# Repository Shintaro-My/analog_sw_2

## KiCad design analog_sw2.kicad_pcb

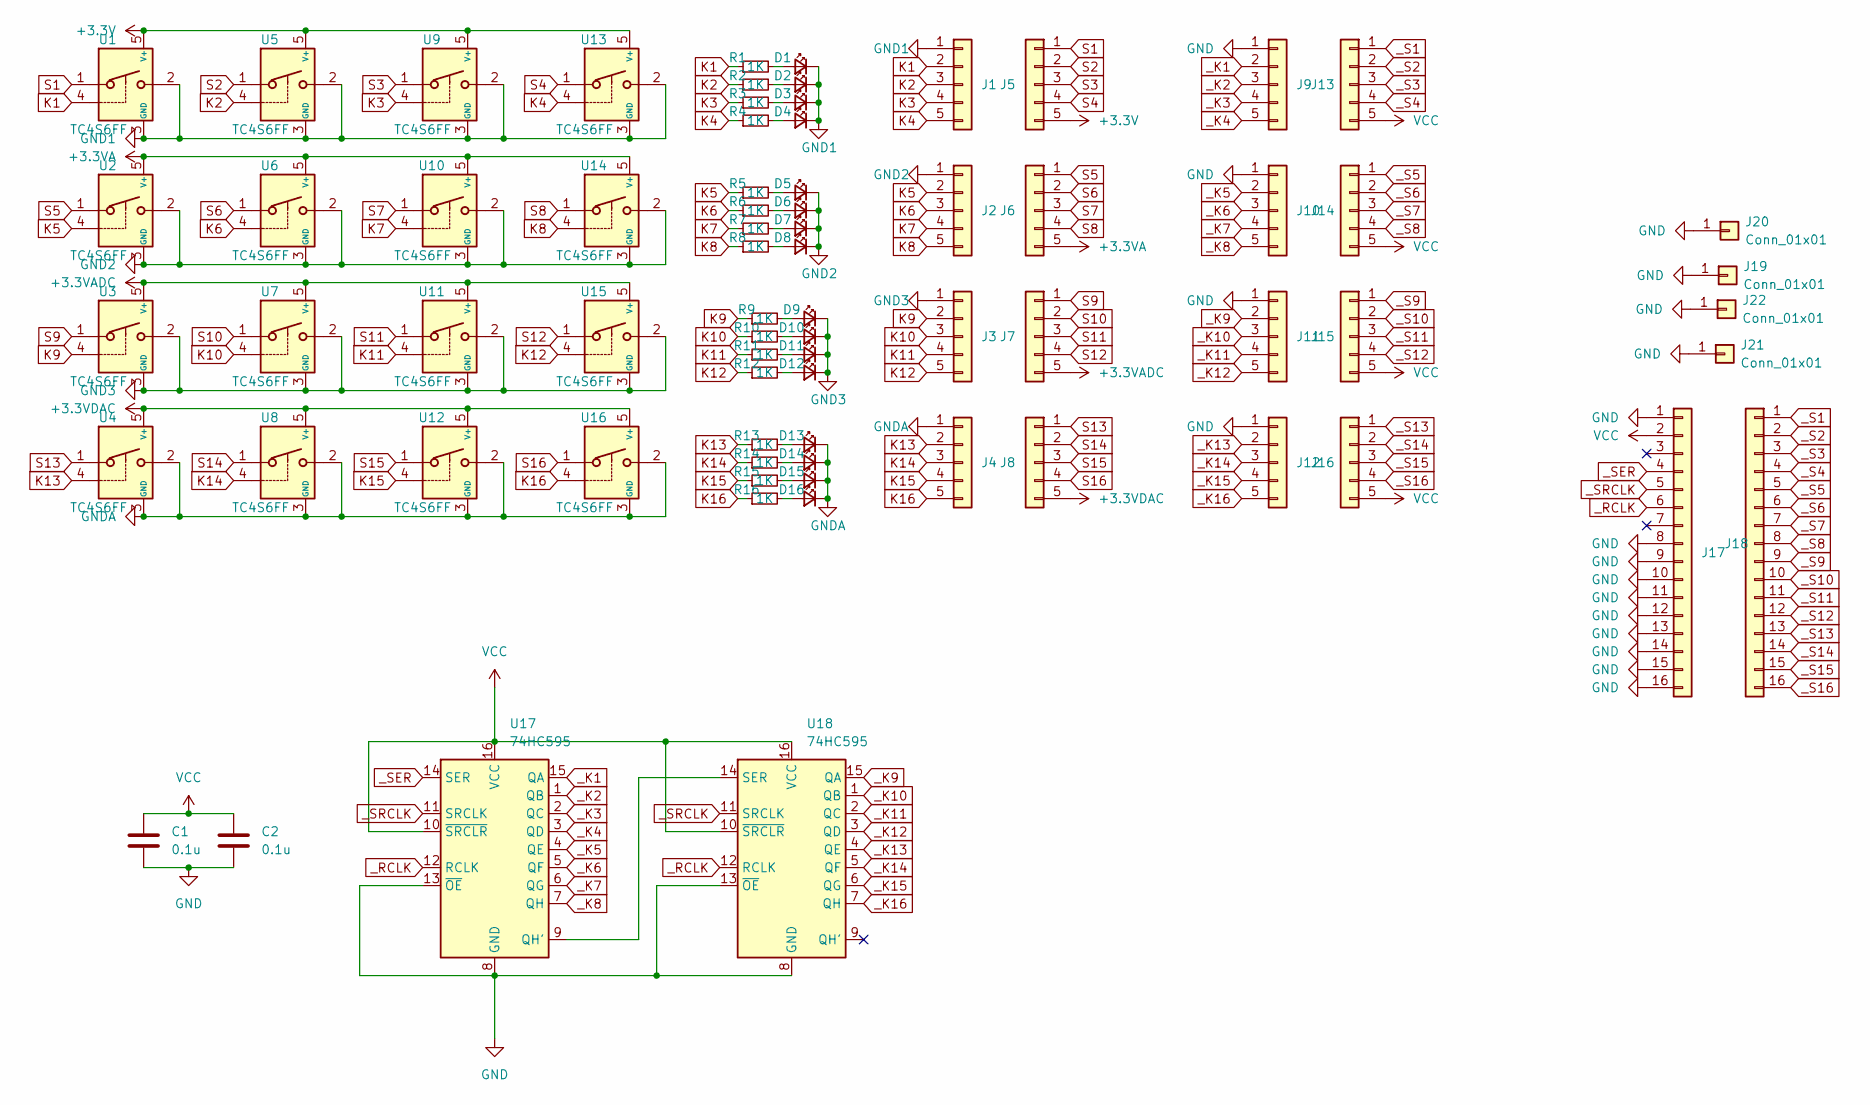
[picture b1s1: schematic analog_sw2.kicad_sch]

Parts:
C1, C2: 0.1u; C_0805_2012Metric
D1, D2, D3, D4, D5, D6, D7, D8, D9, D10, D11, D12, D13, D14, D15, D16: LED_Small; LED_0603_1608Metric_Pad1.05x0.95mm_HandSolder
J1, J2, J3, J4, J5, J6, J7, J8, J9, J10, J11, J12, J13, J14, J15, J16: Conn_01x05; PinHeader_1x05_P2.54mm_Vertical
J17, J18: Conn_01x16; PinHeader_1x16_P2.54mm_Vertical
J19, J20, J21, J22: Conn_01x01; PinHeader_1x01_P2.54mm_Vertical
R1, R2, R3, R4, R5, R6, R7, R8, R9, R10, R11, R12, R13, R14, R15, R16: 1K; R_0603_1608Metric_Pad0.98x0.95mm_HandSolder
U1, U2, U3, U4, U5, U6, U7, U8, U9, U10, U11, U12, U13, U14, U15, U16: TC4S6FF; SOT-23-5
U17, U18: 74HC595; SOP-16_4.55x10.3mm_P1.27mm

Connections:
+3.3V: J5.5, U1.5 (V+), U5.5 (V+), U9.5 (V+), U13.5 (V+)
+3.3VA: J6.5, U2.5 (V+), U6.5 (V+), U10.5 (V+), U14.5 (V+)
+3.3VADC: J7.5, U3.5 (V+), U7.5 (V+), U11.5 (V+), U15.5 (V+)
+3.3VDAC: J8.5, U4.5 (V+), U8.5 (V+), U12.5 (V+), U16.5 (V+)
GND: C1.2, C2.2, J9.1, J10.1, J11.1, J12.1, J17.1, J17.8, J17.9, J17.10, J17.11, J17.12, J17.13, J17.14, J17.15, J17.16, J19.1, J20.1, J21.1, J22.1, U17.8 (GND), U17.13 (~OE), U18.8 (GND), U18.13 (~OE)
GND1: D1.1 (K), D2.1 (K), D3.1 (K), D4.1 (K), J1.1, U1.2, U1.3 (GND), U5.2, U5.3 (GND), U9.2, U9.3 (GND), U13.2, U13.3 (GND)
GND2: D5.1 (K), D6.1 (K), D7.1 (K), D8.1 (K), J2.1, U2.2, U2.3 (GND), U6.2, U6.3 (GND), U10.2, U10.3 (GND), U14.2, U14.3 (GND)
GND3: D9.1 (K), D10.1 (K), D11.1 (K), D12.1 (K), J3.1, U3.2, U3.3 (GND), U7.2, U7.3 (GND), U11.2, U11.3 (GND), U15.2, U15.3 (GND)
GNDA: D13.1 (K), D14.1 (K), D15.1 (K), D16.1 (K), J4.1, U4.2, U4.3 (GND), U8.2, U8.3 (GND), U12.2, U12.3 (GND), U16.2, U16.3 (GND)
K1: J1.2, R1.1, U1.4
K2: J1.3, R2.1, U5.4
K3: J1.4, R3.1, U9.4
K4: J1.5, R4.1, U13.4
K5: J2.2, R5.1, U2.4
K6: J2.3, R6.1, U6.4
K7: J2.4, R7.1, U10.4
K8: J2.5, R8.1, U14.4
K9: J3.2, R9.1, U3.4
K10: J3.3, R10.1, U7.4
K11: J3.4, R11.1, U11.4
K12: J3.5, R12.1, U15.4
K13: J4.2, R13.1, U4.4
K14: J4.3, R14.1, U8.4
K15: J4.4, R15.1, U12.4
K16: J4.5, R16.1, U16.4
unnamed: D1.2 (A), R1.2
unnamed: D2.2 (A), R2.2
unnamed: D3.2 (A), R3.2
unnamed: D4.2 (A), R4.2
unnamed: D5.2 (A), R5.2
unnamed: D6.2 (A), R6.2
unnamed: D7.2 (A), R7.2
unnamed: D8.2 (A), R8.2
unnamed: D9.2 (A), R9.2
unnamed: D10.2 (A), R10.2
unnamed: D11.2 (A), R11.2
unnamed: D12.2 (A), R12.2
unnamed: D13.2 (A), R13.2
unnamed: D14.2 (A), R14.2
unnamed: D15.2 (A), R15.2
unnamed: D16.2 (A), R16.2
unnamed: U17.9 (QH'), U18.14 (SER)
S1: J5.1, U1.1
S2: J5.2, U5.1
S3: J5.3, U9.1
S4: J5.4, U13.1
S5: J6.1, U2.1
S6: J6.2, U6.1
S7: J6.3, U10.1
S8: J6.4, U14.1
S9: J7.1, U3.1
S10: J7.2, U7.1
S11: J7.3, U11.1
S12: J7.4, U15.1
S13: J8.1, U4.1
S14: J8.2, U8.1
S15: J8.3, U12.1
S16: J8.4, U16.1
VCC: C1.1, C2.1, J13.5, J14.5, J15.5, J16.5, J17.2, U17.10 (~SRCLR), U17.16 (VCC), U18.10 (~SRCLR), U18.16 (VCC)
_K1: J9.2, U17.15 (QA)
_K2: J9.3, U17.1 (QB)
_K3: J9.4, U17.2 (QC)
_K4: J9.5, U17.3 (QD)
_K5: J10.2, U17.4 (QE)
_K6: J10.3, U17.5 (QF)
_K7: J10.4, U17.6 (QG)
_K8: J10.5, U17.7 (QH)
_K9: J11.2, U18.15 (QA)
_K10: J11.3, U18.1 (QB)
_K11: J11.4, U18.2 (QC)
_K12: J11.5, U18.3 (QD)
_K13: J12.2, U18.4 (QE)
_K14: J12.3, U18.5 (QF)
_K15: J12.4, U18.6 (QG)
_K16: J12.5, U18.7 (QH)
_RCLK: J17.6, U17.12 (RCLK), U18.12 (RCLK)
_S1: J13.1, J18.1
_S2: J13.2, J18.2
_S3: J13.3, J18.3
_S4: J13.4, J18.4
_S5: J14.1, J18.5
_S6: J14.2, J18.6
_S7: J14.3, J18.7
_S8: J14.4, J18.8
_S9: J15.1, J18.9
_S10: J15.2, J18.10
_S11: J15.3, J18.11
_S12: J15.4, J18.12
_S13: J16.1, J18.13
_S14: J16.2, J18.14
_S15: J16.3, J18.15
_S16: J16.4, J18.16
_SER: J17.4, U17.14 (SER)
_SRCLK: J17.5, U17.11 (SRCLK), U18.11 (SRCLK)

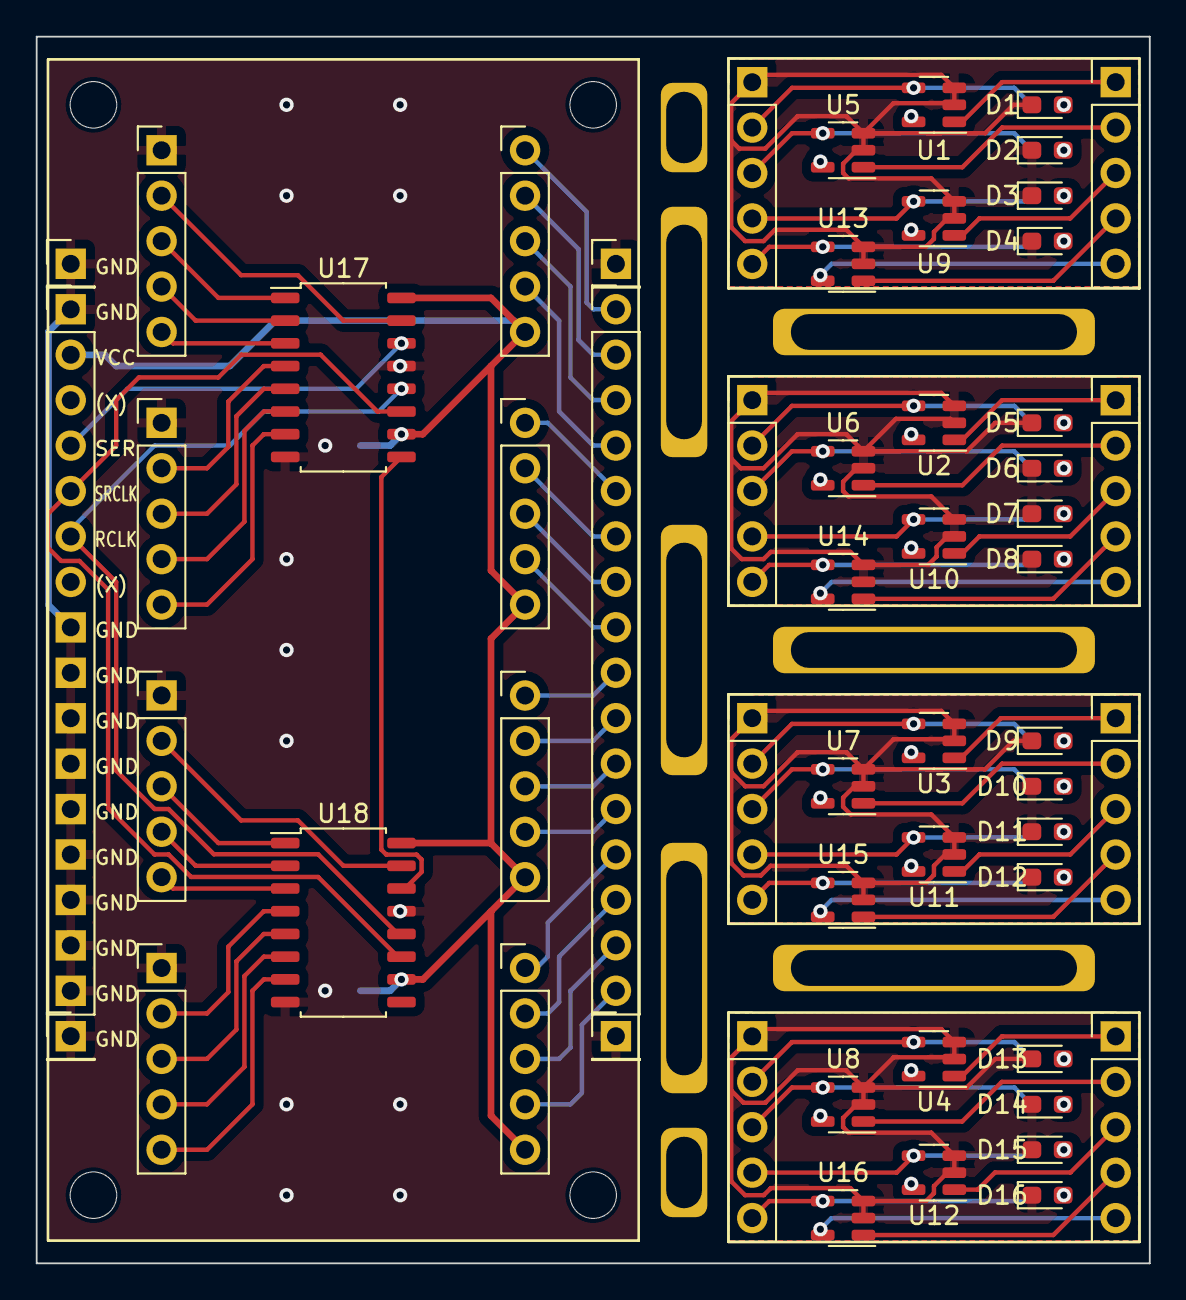
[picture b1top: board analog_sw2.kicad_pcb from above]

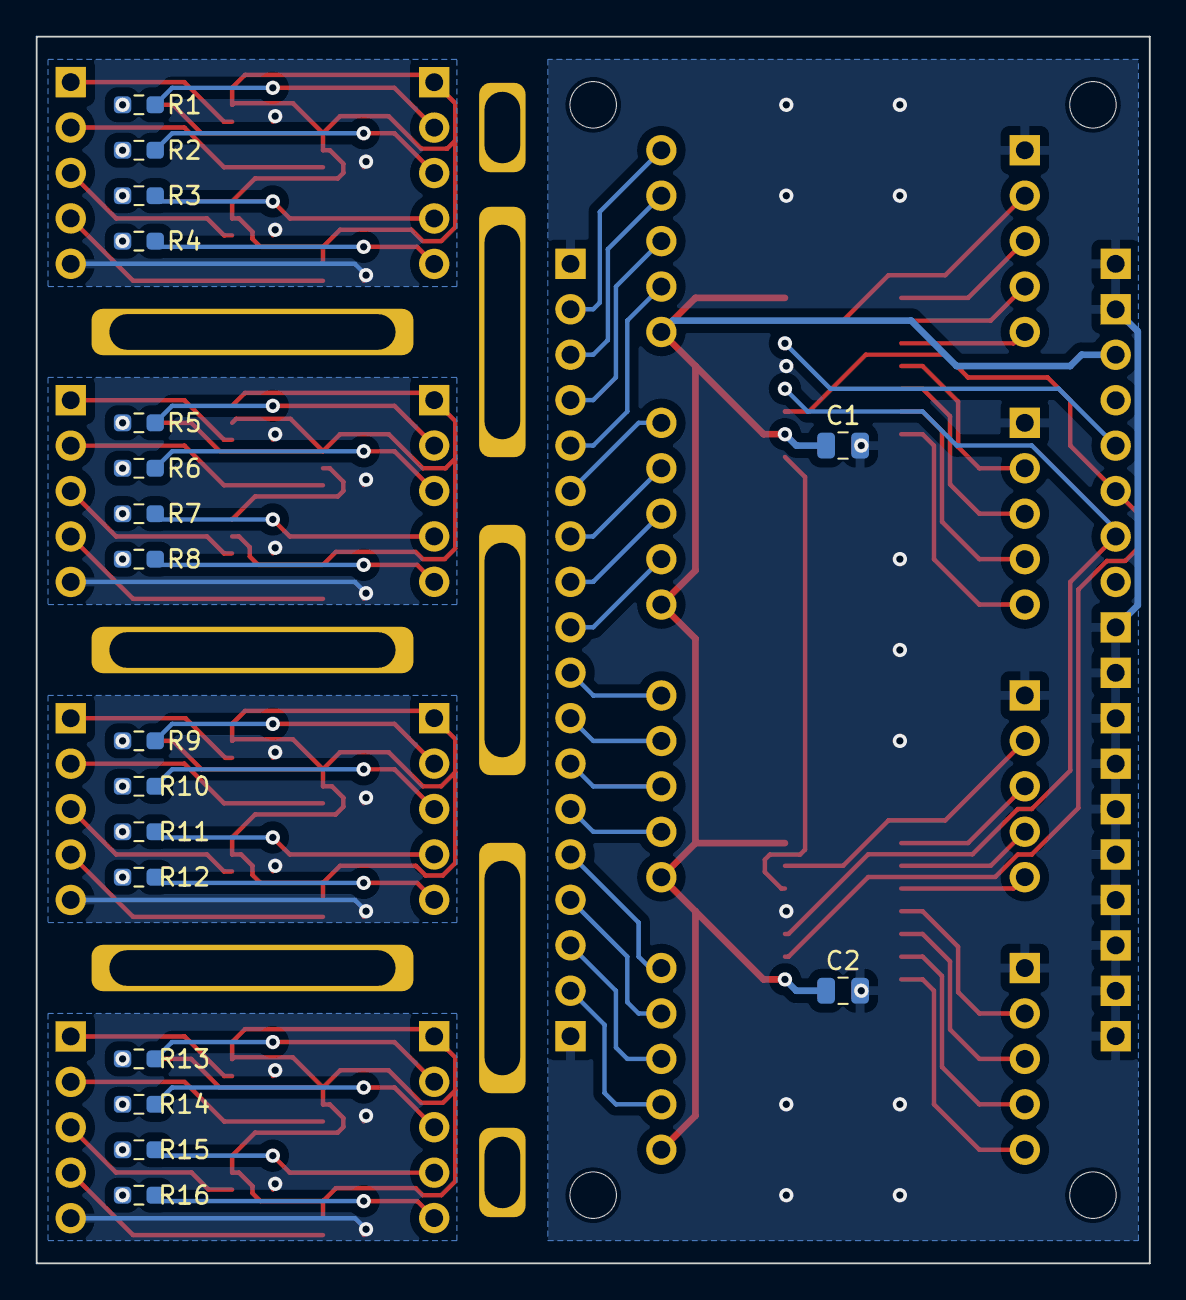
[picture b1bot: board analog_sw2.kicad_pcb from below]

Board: 2 copper layers, 62.2 x 68.6 mm, 82 parts (18 on the bottom side), 94 nets.

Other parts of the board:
P1, P2, P3, P4, P5, P6, P7: (no value)
P8: NEJI_2.6mm
